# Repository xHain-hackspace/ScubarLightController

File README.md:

# ScubarLightController
PCB board design for xHain scubar LEDs.

Original design: https://github.com/blejdfist/xHain_ScubarLightController

# Hardware Prototype 
</img>

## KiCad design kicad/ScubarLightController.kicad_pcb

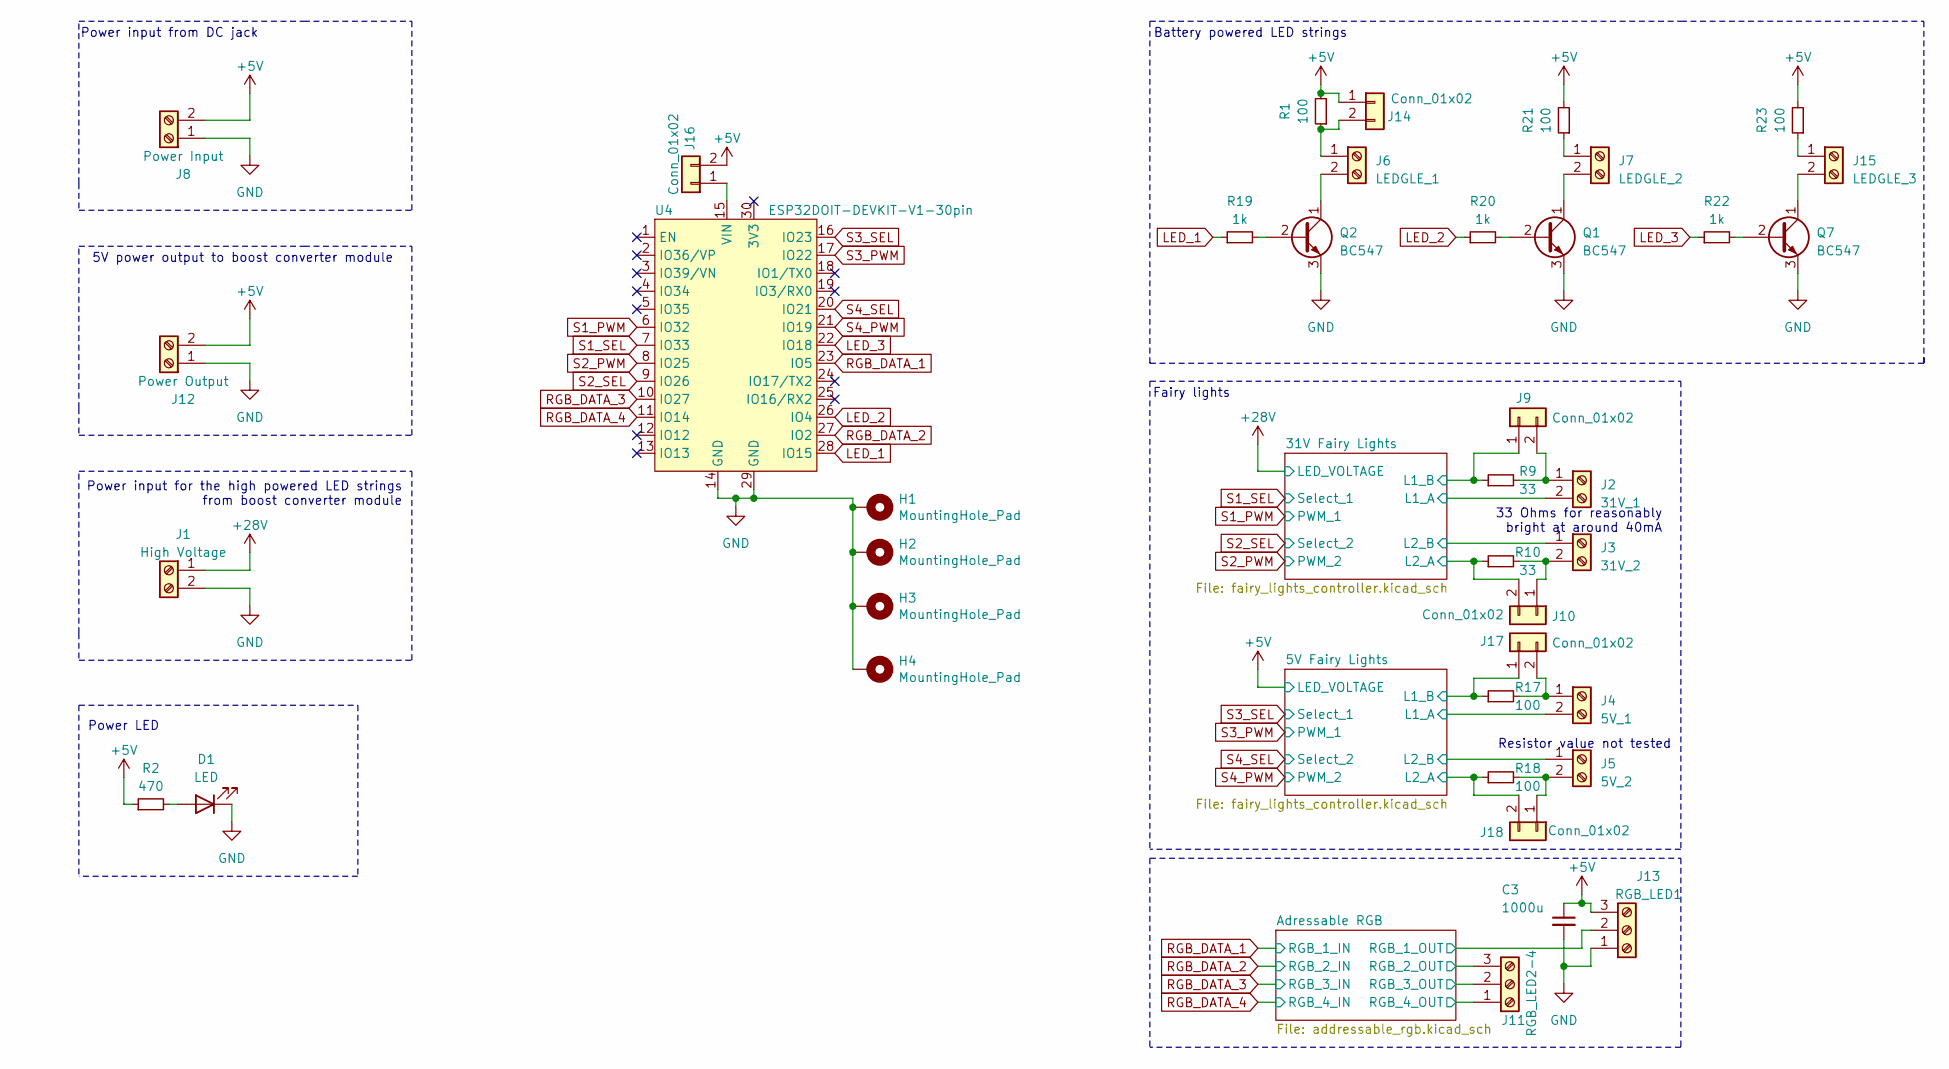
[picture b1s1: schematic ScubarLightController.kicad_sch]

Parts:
C3: 1000u; C_0805_2012Metric
D1: LED; LED_D5.0mm
H1, H2, H3, H4: MountingHole_Pad; MountingHole_3.2mm_M3_Pad_Via
J1: High Voltage; TerminalBlock_Phoenix_MKDS-1,5-2_1x02_P5.00mm_Horizontal
J2: 31V_1; TerminalBlock_Phoenix_MKDS-1,5-2_1x02_P5.00mm_Horizontal
J3: 31V_2; TerminalBlock_Phoenix_MKDS-1,5-2_1x02_P5.00mm_Horizontal
J4: 5V_1; TerminalBlock_Phoenix_MKDS-1,5-2_1x02_P5.00mm_Horizontal
J5: 5V_2; TerminalBlock_Phoenix_MKDS-1,5-2_1x02_P5.00mm_Horizontal
J6: LEDGLE_1; TerminalBlock_Phoenix_MKDS-1,5-2_1x02_P5.00mm_Horizontal
J7: LEDGLE_2; TerminalBlock_Phoenix_MKDS-1,5-2_1x02_P5.00mm_Horizontal
J8: Power Input; TerminalBlock_Phoenix_MKDS-1,5-2_1x02_P5.00mm_Horizontal
J9, J10, J14, J16, J17, J18: Conn_01x02; PinHeader_1x02_P2.54mm_Vertical
J11: RGB_LED2-4; TerminalBlock_Phoenix_MKDS-1,5-3_1x03_P5.00mm_Horizontal
J12: Power Output; TerminalBlock_Phoenix_MKDS-1,5-2_1x02_P5.00mm_Horizontal
J13: RGB_LED1; TerminalBlock_Phoenix_MKDS-1,5-3_1x03_P5.00mm_Horizontal
J15: LEDGLE_3; TerminalBlock_Phoenix_MKDS-1,5-2_1x02_P5.00mm_Horizontal
Q1, Q2, Q7: BC547; TO-92_Inline
R1, R17, R18, R21, R23: 100; R_Axial_DIN0204_L3.6mm_D1.6mm_P5.08mm_Horizontal
R2: 470; R_Axial_DIN0204_L3.6mm_D1.6mm_P5.08mm_Horizontal
R9, R10: 33; R_Axial_DIN0204_L3.6mm_D1.6mm_P5.08mm_Horizontal
R19, R20, R22: 1k; R_Axial_DIN0204_L3.6mm_D1.6mm_P5.08mm_Horizontal
U4: ESP32DOIT-DEVKIT-V1-30pin

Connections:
+5V: C3.1, J8.2, J12.2, J13.3, J14.1, J16.2, R1.2, R2.1, R21.2, R23.2; also elsewhere on the board
+28V: J1.1; also elsewhere on the board
/5V Fairy Lights/L1_A: J4.2; also elsewhere on the board
/5V Fairy Lights/L1_B: J17.1, R17.1; also elsewhere on the board
/5V Fairy Lights/L2_A: J18.2, R18.1; also elsewhere on the board
/5V Fairy Lights/L2_B: J5.1; also elsewhere on the board
/31V Fairy Lights/L1_A: J2.2; also elsewhere on the board
/31V Fairy Lights/L1_B: J9.1, R9.1; also elsewhere on the board
/31V Fairy Lights/L2_A: J10.2, R10.1; also elsewhere on the board
/31V Fairy Lights/L2_B: J3.1; also elsewhere on the board
/Adressable RGB/RGB_1_OUT: J13.2; also elsewhere on the board
/Adressable RGB/RGB_2_OUT: J11.3; also elsewhere on the board
/Adressable RGB/RGB_3_OUT: J11.2; also elsewhere on the board
/Adressable RGB/RGB_4_OUT: J11.1; also elsewhere on the board
GND: C3.2, D1.1 (K), H1.1, H2.1, H3.1, H4.1, J1.2, J8.1, J12.1, J13.1, Q1.3 (E), Q2.3 (E), Q7.3 (E), U4.14 (GND), U4.29 (GND); also elsewhere on the board
LED_1: R19.1, U4.28 (IO15)
LED_2: R20.1, U4.26 (IO4)
LED_3: R22.1, U4.22 (IO18)
unnamed: D1.2 (A), R2.2
unnamed: J2.1, J9.2, R9.2
unnamed: J6.2, Q2.1 (C)
unnamed: J7.1, R21.1
unnamed: J7.2, Q1.1 (C)
unnamed: J3.2, J10.1, R10.2
unnamed: J6.1, J14.2, R1.1
unnamed: J15.1, R23.1
unnamed: J15.2, Q7.1 (C)
unnamed: J16.1, U4.15 (VIN)
unnamed: J4.1, J17.2, R17.2
unnamed: J5.2, J18.1, R18.2
unnamed: Q1.2 (B), R20.2
unnamed: Q2.2 (B), R19.2
unnamed: Q7.2 (B), R22.2
RGB_DATA_1: U4.23 (IO5); also elsewhere on the board
RGB_DATA_2: U4.27 (IO2); also elsewhere on the board
RGB_DATA_3: U4.10 (IO27); also elsewhere on the board
RGB_DATA_4: U4.11 (IO14); also elsewhere on the board
S1_PWM: U4.6 (IO32); also elsewhere on the board
S1_SEL: U4.7 (IO33); also elsewhere on the board
S2_PWM: U4.8 (IO25); also elsewhere on the board
S2_SEL: U4.9 (IO26); also elsewhere on the board
S3_PWM: U4.17 (IO22); also elsewhere on the board
S3_SEL: U4.16 (IO23); also elsewhere on the board
S4_PWM: U4.21 (IO19); also elsewhere on the board
S4_SEL: U4.20 (IO21); also elsewhere on the board

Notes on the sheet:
Power LED
Power input from DC jack
5V power output to boost converter module
Power input for the high powered LED strings from boost converter module
Fairy lights
Battery powered LED strings
33 Ohms for reasonably bright at around 40mA
Resistor value not tested

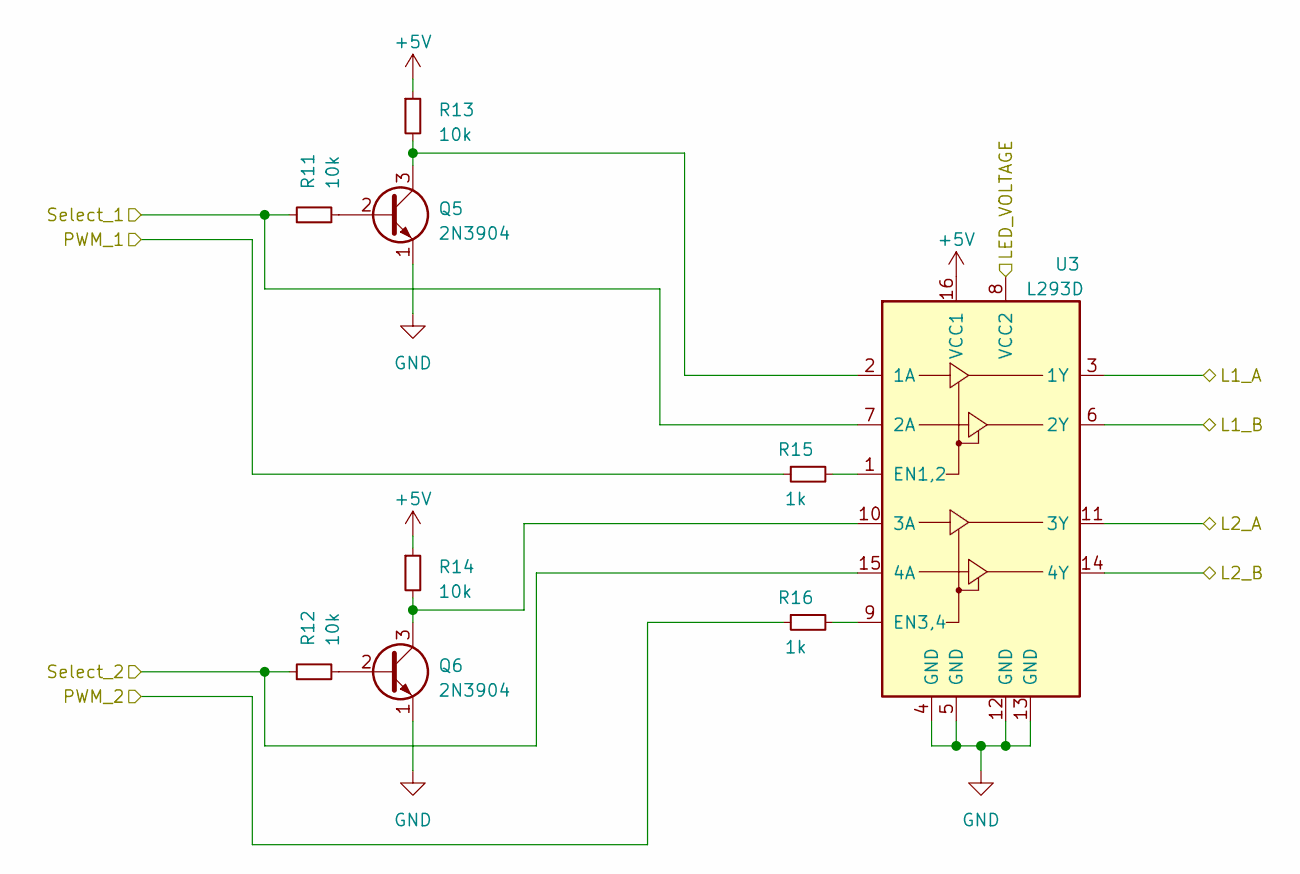
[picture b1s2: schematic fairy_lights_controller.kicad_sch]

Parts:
Q5, Q6: 2N3904; TO-92_Inline
R11, R12, R13, R14: 10k; R_Axial_DIN0204_L3.6mm_D1.6mm_P5.08mm_Horizontal
R15, R16: 1k; R_Axial_DIN0204_L3.6mm_D1.6mm_P5.08mm_Horizontal
U3: L293D; DIP-16_W7.62mm

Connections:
+5V: R13.1, R14.1, U3.16 (VCC1); also elsewhere on the board
+28V: U3.8 (VCC2); also elsewhere on the board
/31V Fairy Lights/L1_A: U3.3 (1Y); also elsewhere on the board
/31V Fairy Lights/L1_B: U3.6 (2Y); also elsewhere on the board
/31V Fairy Lights/L2_A: U3.11 (3Y); also elsewhere on the board
/31V Fairy Lights/L2_B: U3.14 (4Y); also elsewhere on the board
GND: Q5.1 (E), Q6.1 (E), U3.4 (GND), U3.5 (GND), U3.12 (GND), U3.13 (GND); also elsewhere on the board
unnamed: Q5.2 (B), R11.2
unnamed: Q5.3 (C), R13.2, U3.2 (1A)
unnamed: Q6.2 (B), R12.2
unnamed: Q6.3 (C), R14.2, U3.10 (3A)
unnamed: R15.2, U3.1 (EN1,2)
unnamed: R16.2, U3.9 (EN3,4)
S1_PWM: R15.1; also elsewhere on the board
S1_SEL: R11.1, U3.7 (2A); also elsewhere on the board
S2_PWM: R16.1; also elsewhere on the board
S2_SEL: R12.1, U3.15 (4A); also elsewhere on the board

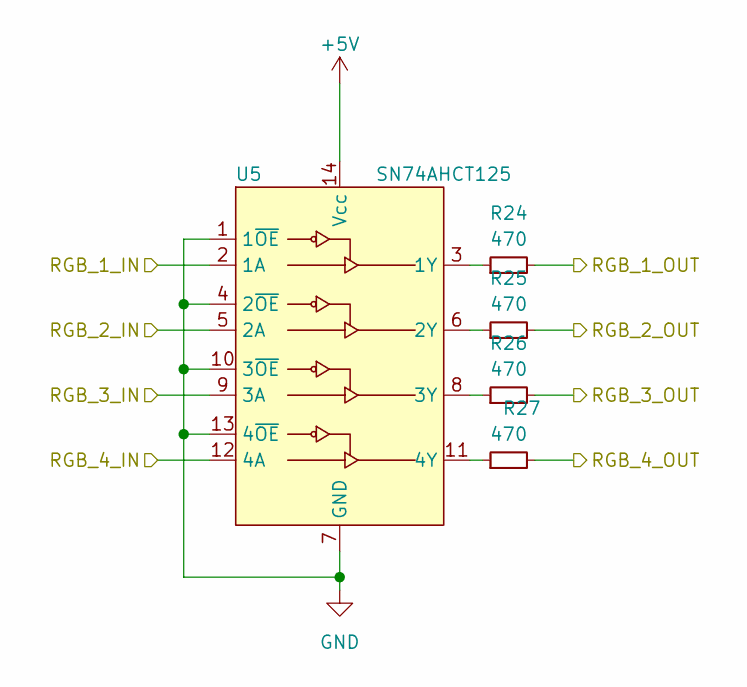
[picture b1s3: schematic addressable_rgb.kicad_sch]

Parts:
R24, R25, R26, R27: 470; R_0805_2012Metric
U5: SN74AHCT125; DIP-14_W7.62mm

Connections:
+5V: U5.14 (Vcc); also elsewhere on the board
/Adressable RGB/RGB_1_OUT: R24.2; also elsewhere on the board
/Adressable RGB/RGB_2_OUT: R25.2; also elsewhere on the board
/Adressable RGB/RGB_3_OUT: R26.2; also elsewhere on the board
/Adressable RGB/RGB_4_OUT: R27.2; also elsewhere on the board
GND: U5.1 (1~OE), U5.4 (2~OE), U5.7 (GND), U5.10 (3~OE), U5.13 (4~OE); also elsewhere on the board
unnamed: R24.1, U5.3 (1Y)
unnamed: R25.1, U5.6 (2Y)
unnamed: R26.1, U5.8 (3Y)
unnamed: R27.1, U5.11 (4Y)
RGB_DATA_1: U5.2 (1A); also elsewhere on the board
RGB_DATA_2: U5.5 (2A); also elsewhere on the board
RGB_DATA_3: U5.9 (3A); also elsewhere on the board
RGB_DATA_4: U5.12 (4A); also elsewhere on the board

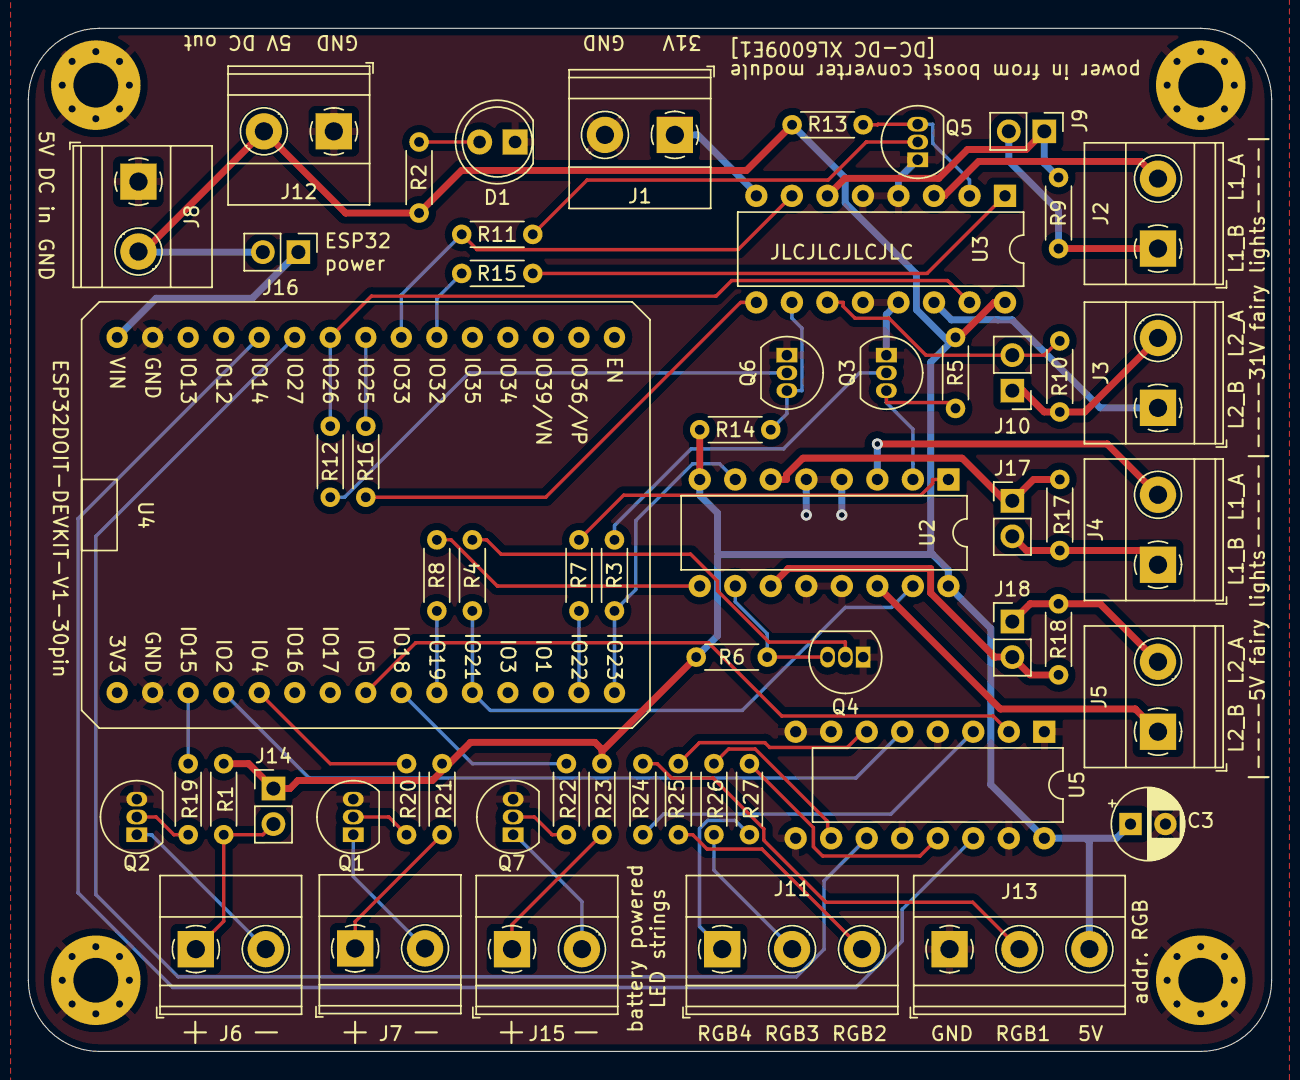
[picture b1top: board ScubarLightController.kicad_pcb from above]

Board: 2 copper layers, 88.9 x 73.2 mm, 62 parts (0 on the bottom side), 61 nets.

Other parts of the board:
Q3, Q4: 2N3904; TO-92_Inline
R3, R4, R5, R6: 10k; R_Axial_DIN0204_L3.6mm_D1.6mm_P5.08mm_Horizontal
R7, R8: 1k; R_Axial_DIN0204_L3.6mm_D1.6mm_P5.08mm_Horizontal
U2: L293D; DIP-16_W7.62mm

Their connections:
+5V: R5.1, R6.1, U2.8 (VCC2), U2.16 (VCC1); also elsewhere on the board
/5V Fairy Lights/L1_A: U2.3 (1Y); also elsewhere on the board
/5V Fairy Lights/L1_B: U2.6 (2Y); also elsewhere on the board
/5V Fairy Lights/L2_A: U2.11 (3Y); also elsewhere on the board
/5V Fairy Lights/L2_B: U2.14 (4Y); also elsewhere on the board
GND: Q3.1 (E), Q4.1 (E), U2.4 (GND), U2.5 (GND), U2.12 (GND), U2.13 (GND); also elsewhere on the board
unnamed: Q3.2 (B), R3.2
unnamed: Q3.3 (C), R5.2, U2.2 (1A)
unnamed: Q4.2 (B), R4.2
unnamed: Q4.3 (C), R6.2, U2.10 (3A)
unnamed: R7.2, U2.1 (EN1,2)
unnamed: R8.2, U2.9 (EN3,4)
S3_PWM: R7.1; also elsewhere on the board
S3_SEL: R3.1, U2.7 (2A); also elsewhere on the board
S4_PWM: R8.1; also elsewhere on the board
S4_SEL: R4.1, U2.15 (4A); also elsewhere on the board

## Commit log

2021-08-12 reworked board design from https://github.com/blejdfist/xHain_ScubarLightController
2021-08-12 minor changes to silkscreen
2021-08-12 widened power trace widths
2021-08-12 added prototype image
2021-08-29 removed 5V power regulator, added resistor pins
2021-08-29 added logo and gerber files
2021-09-13 finalised board with RGB-LED:2-4 pins
2021-09-13 fixed bad labels
2021-09-14 fixed silkscreen and added power jumper
